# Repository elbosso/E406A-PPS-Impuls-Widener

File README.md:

# E406A-PPS-Impuls-Widener

<!---

--->

This is a project i needed for building my own stratum-0-NTP server using a Raspberry Pi: I used some components i had lying around - among them a SIRF III Receiver E406A. But to get a really accurate clock, one needs not only the GPS-Time but also the PPS Signal. This signal is provided by the E406A but the spike is way to short and its level is way to low for the raspberry to detect it on one of its GPIOs and in turn to trigger an interrupt.

So, i tried what i could with an NE555 - it detects the PPS and i used it to make it to last for approximately 0.3 seconds. The led really is only for people who like blinkenlights, the transistor is there because the NE555 starts with a falling sinal on trig - because the PPS from the E406A is rising I needed a simple inverter.

# Images of the PCB (images created automatically with GitHub actions provided by [kicad render action](https://github.com/linalinn/kicad-render?tab=readme-ov-file))

### Images

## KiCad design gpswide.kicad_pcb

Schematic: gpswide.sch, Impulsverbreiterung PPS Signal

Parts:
C1, C2: 1u; CP_Radial_D4.0mm_P1.50mm
D1: LED; LED_D3.0mm
J1: GPS E406A; PinHeader_1x08_P2.54mm_Vertical
J2: Raspberry Pi; PinSocket_2x08_P2.54mm_Vertical
Q1: 2N3904; TO-92_Inline
R1: 3K3; R_Axial_DIN0207_L6.3mm_D2.5mm_P7.62mm_Horizontal
R2: 10K; R_Axial_DIN0207_L6.3mm_D2.5mm_P7.62mm_Horizontal
R3: 270K; R_Axial_DIN0207_L6.3mm_D2.5mm_P7.62mm_Horizontal
R4: 100K; R_Axial_DIN0207_L6.3mm_D2.5mm_P7.62mm_Horizontal
R5: 330R; R_Axial_DIN0207_L6.3mm_D2.5mm_P7.62mm_Horizontal
U1: NE555; DIP-8_W7.62mm

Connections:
GND: C1.2, C2.2, D1.1, J1.6, J2.6, Q1.1, U1.1 (GND)
GPS_PPS: J1.1, R2.2
GPS_TX: J1.3, J2.10
GPS_VCC: J1.5, J2.4, R1.1, R3.2, R4.1, U1.4 (R), U1.8 (VCC)
unnamed: C1.1, U1.5 (CV)
unnamed: C2.1, R3.1, U1.6 (THR), U1.7 (DIS)
unnamed: Q1.2, R2.1
unnamed: Q1.3, R1.2, U1.2 (TR)
unnamed: R4.2, R5.2, U1.3 (Q)
RPI_PPS: D1.2, J2.7, R5.1

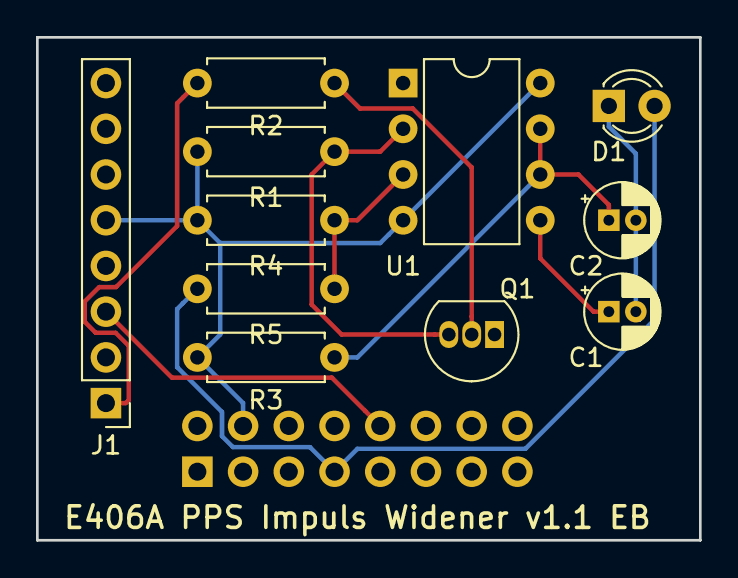
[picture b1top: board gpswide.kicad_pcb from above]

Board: 2 copper layers, 36.8 x 27.9 mm, 12 parts (1 on the bottom side), 10 nets.

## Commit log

2018-08-12 Initial checkin
2018-08-12 create LICENSE
2018-08-12 some 3d screenshots
2018-08-12 cleaned up
2018-08-13 ground plane added
2018-10-14 v 1.1: Transistor footprint changed, resistor value changed
2019-01-04 badges added
2022-01-02 pdf for documentation purposes
2024-03-25 indentation fixes (?)
2024-03-25 testing the rendered images
